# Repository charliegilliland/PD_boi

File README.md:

# PD_boi

This is a simple demo of the FUSB302 with STM32G030.
The device can negotiate an output voltage with a USB-C PD source.

The firmware is based on the [PD_micro](https://github.com/ryan-ma/PD_Micro) code, with the approproate changes to support the STM32.

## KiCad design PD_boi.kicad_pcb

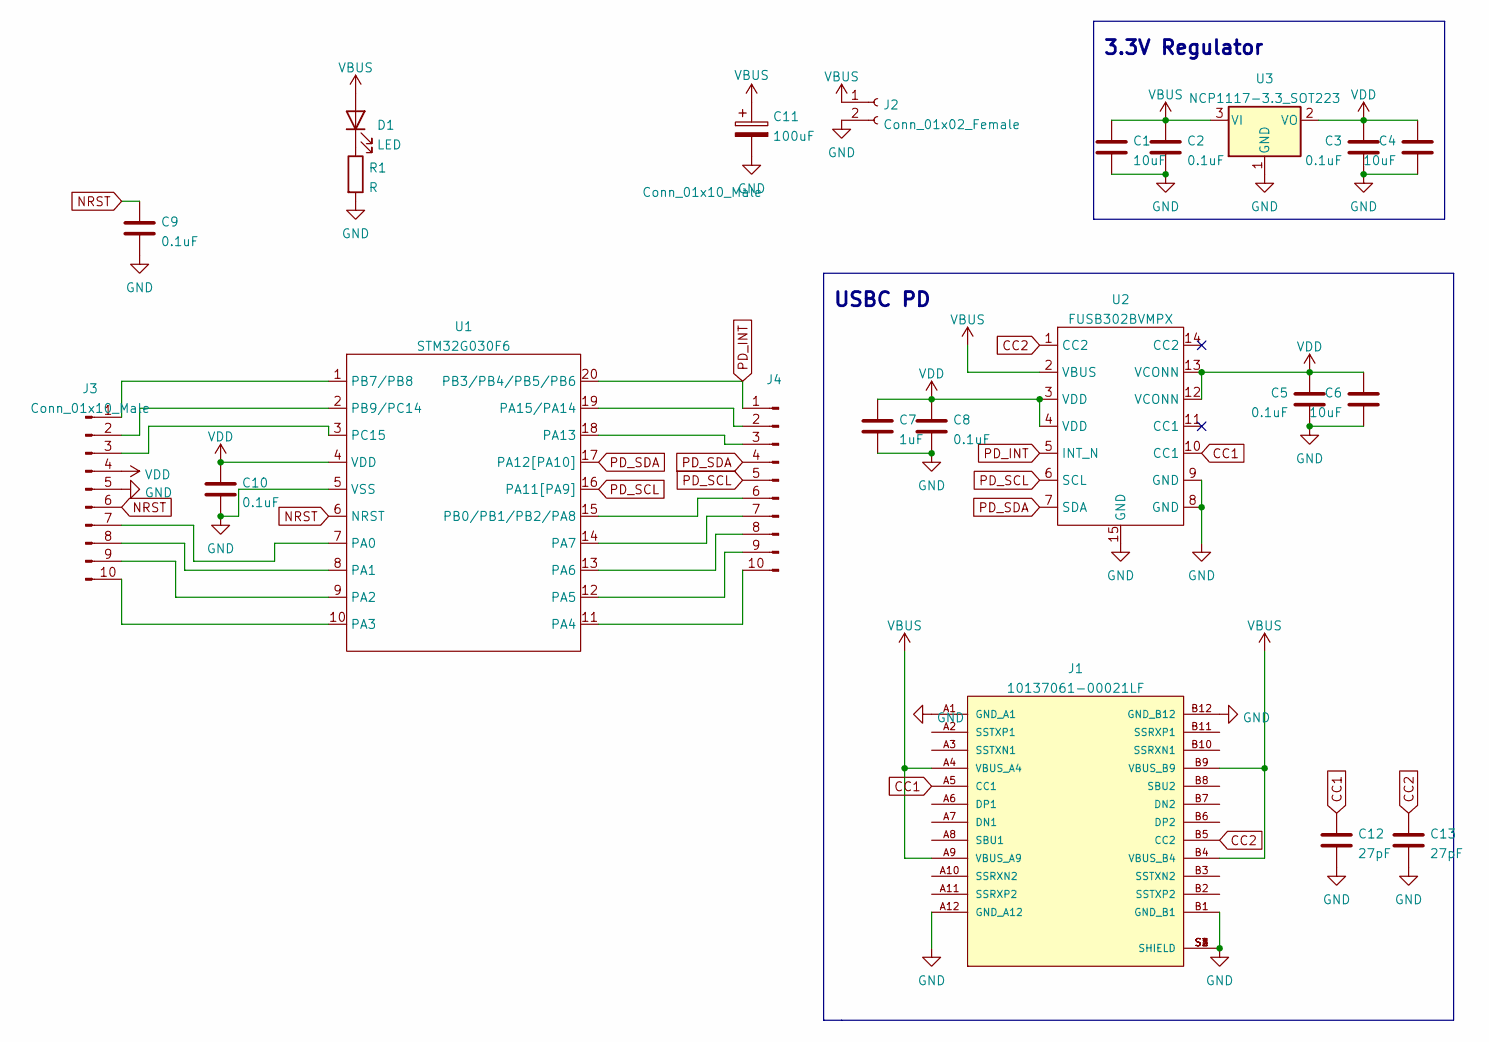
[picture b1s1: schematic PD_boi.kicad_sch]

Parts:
C1, C4, C6: 10uF; C_0603_1608Metric
C2, C3, C5, C8, C9, C10: 0.1uF; C_0603_1608Metric
C7: 1uF; C_0603_1608Metric
C11: 100uF; CP_Elec_6.3x7.7
C12, C13: 27pF; C_0603_1608Metric
D1: LED; LED_0805_2012Metric
J1: 10137061-00021LF; AMPHENOL_10137061-00021LF; PARTREV C
J2: Conn_01x02_Female; TerminalBlock_Phoenix_PT-1,5-2-5.0-H_1x02_P5.00mm_Horizontal
J3, J4: Conn_01x10_Male; PinHeader_1x10_P2.54mm_Vertical
R1: R; R_0603_1608Metric
U1: STM32G030F6; TSSOP-20_4.4x6.5mm_P0.65mm
U2: FUSB302BVMPX; WQFN-14-1EP_2.5x2.5mm_P0.5mm_EP1.45x1.45mm
U3: NCP1117-3.3_SOT223; SOT-223-3_TabPin2

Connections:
CC1: C12.1, J1.A5 (CC1), U2.10 (CC1)
CC2: C13.1, J1.B5 (CC2), U2.1 (CC2)
GND: C1.2, C2.2, C3.2, C4.2, C5.2, C6.2, C7.2, C8.2, C9.2, C10.2, C11.2, C12.2, C13.2, J1.A1 (GND_A1), J1.A12 (GND_A12), J1.B1 (GND_B1), J1.B12 (GND_B12), J1.S1 (SHIELD), J1.S2 (SHIELD), J1.S3 (SHIELD), J1.S4 (SHIELD), J2.2, J3.5, R1.2, U1.5 (VSS), U2.8 (GND), U2.9 (GND), U2.15 (GND), U3.1 (GND)
NRST: C9.1, J3.6, U1.6 (NRST)
unnamed: D1.1 (K), R1.1
unnamed: J3.1, U1.1 (PB7/PB8)
unnamed: J3.2, U1.2 (PB9/PC14)
unnamed: J3.3, U1.3 (PC15)
unnamed: J3.7, U1.7 (PA0)
unnamed: J3.8, U1.8 (PA1)
unnamed: J3.9, U1.9 (PA2)
unnamed: J3.10, U1.10 (PA3)
unnamed: J4.2, U1.19 (PA15/PA14)
unnamed: J4.3, U1.18 (PA13)
unnamed: J4.6, U1.15 (PB0/PB1/PB2/PA8)
unnamed: J4.7, U1.14 (PA7)
unnamed: J4.8, U1.13 (PA6)
unnamed: J4.9, U1.12 (PA5)
unnamed: J4.10, U1.11 (PA4)
PD_INT: J4.1, U1.20 (PB3/PB4/PB5/PB6), U2.5 (INT_N)
PD_SCL: J4.5, U1.16 (PA11[PA9]), U2.6 (SCL)
PD_SDA: J4.4, U1.17 (PA12[PA10]), U2.7 (SDA)
VBUS: C1.1, C2.1, C11.1, D1.2 (A), J1.A4 (VBUS_A4), J1.A9 (VBUS_A9), J1.B4 (VBUS_B4), J1.B9 (VBUS_B9), J2.1, U2.2 (VBUS), U3.3 (VI)
VDD: C3.1, C4.1, C5.1, C6.1, C7.1, C8.1, C10.1, J3.4, U1.4 (VDD), U2.3 (VDD), U2.4 (VDD), U2.12 (VCONN), U2.13 (VCONN), U3.2 (VO)

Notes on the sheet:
USBC PD
3.3V Regulator

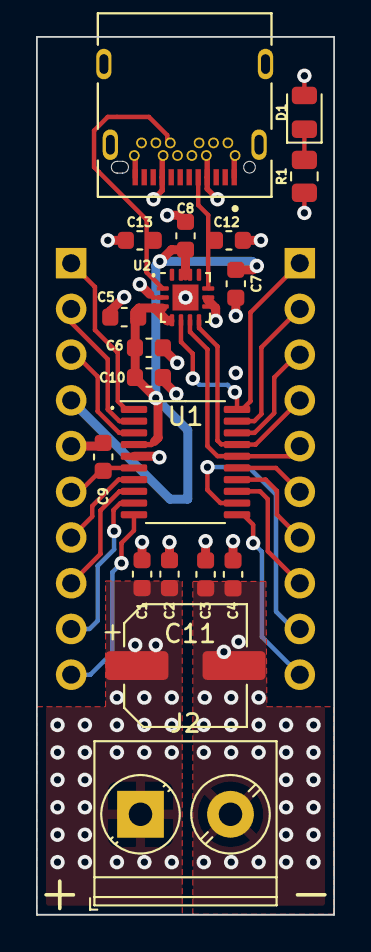
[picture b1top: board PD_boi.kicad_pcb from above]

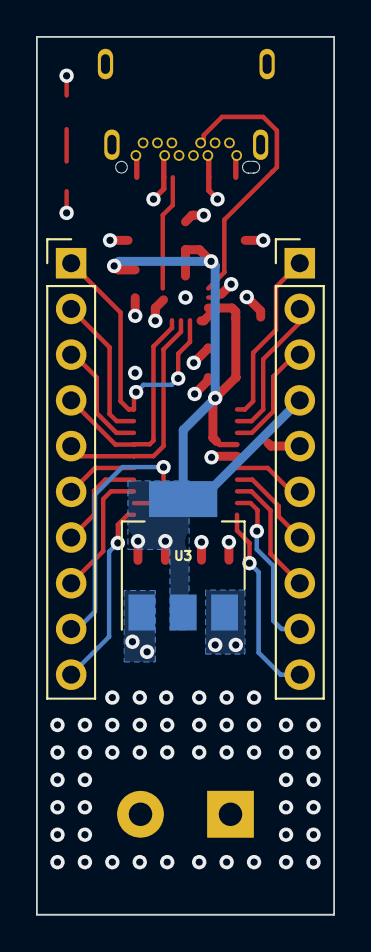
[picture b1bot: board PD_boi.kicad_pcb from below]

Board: 4 copper layers, 16.5 x 48.8 mm, 22 parts (3 on the bottom side), 24 nets.
